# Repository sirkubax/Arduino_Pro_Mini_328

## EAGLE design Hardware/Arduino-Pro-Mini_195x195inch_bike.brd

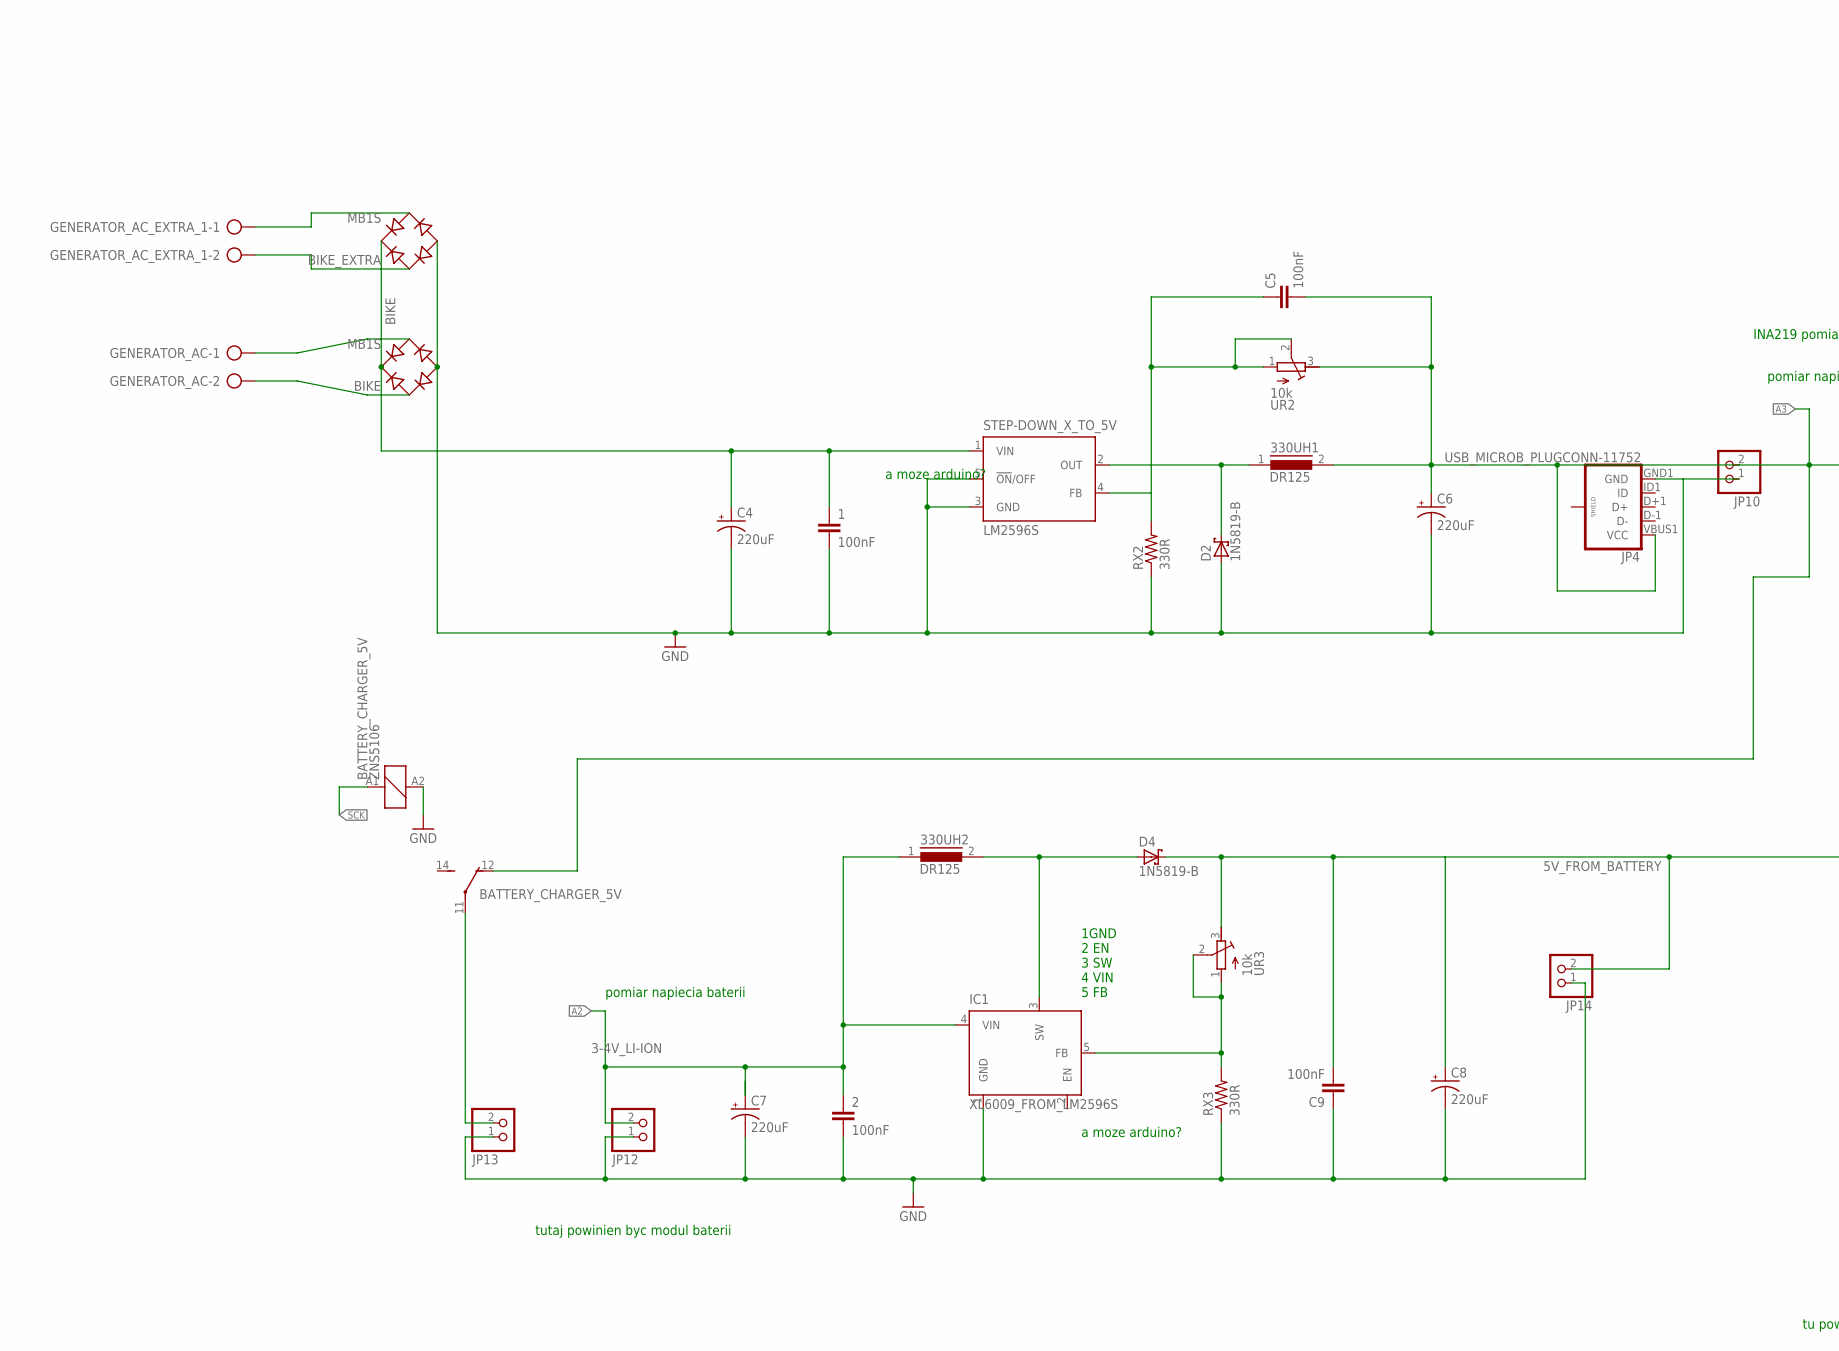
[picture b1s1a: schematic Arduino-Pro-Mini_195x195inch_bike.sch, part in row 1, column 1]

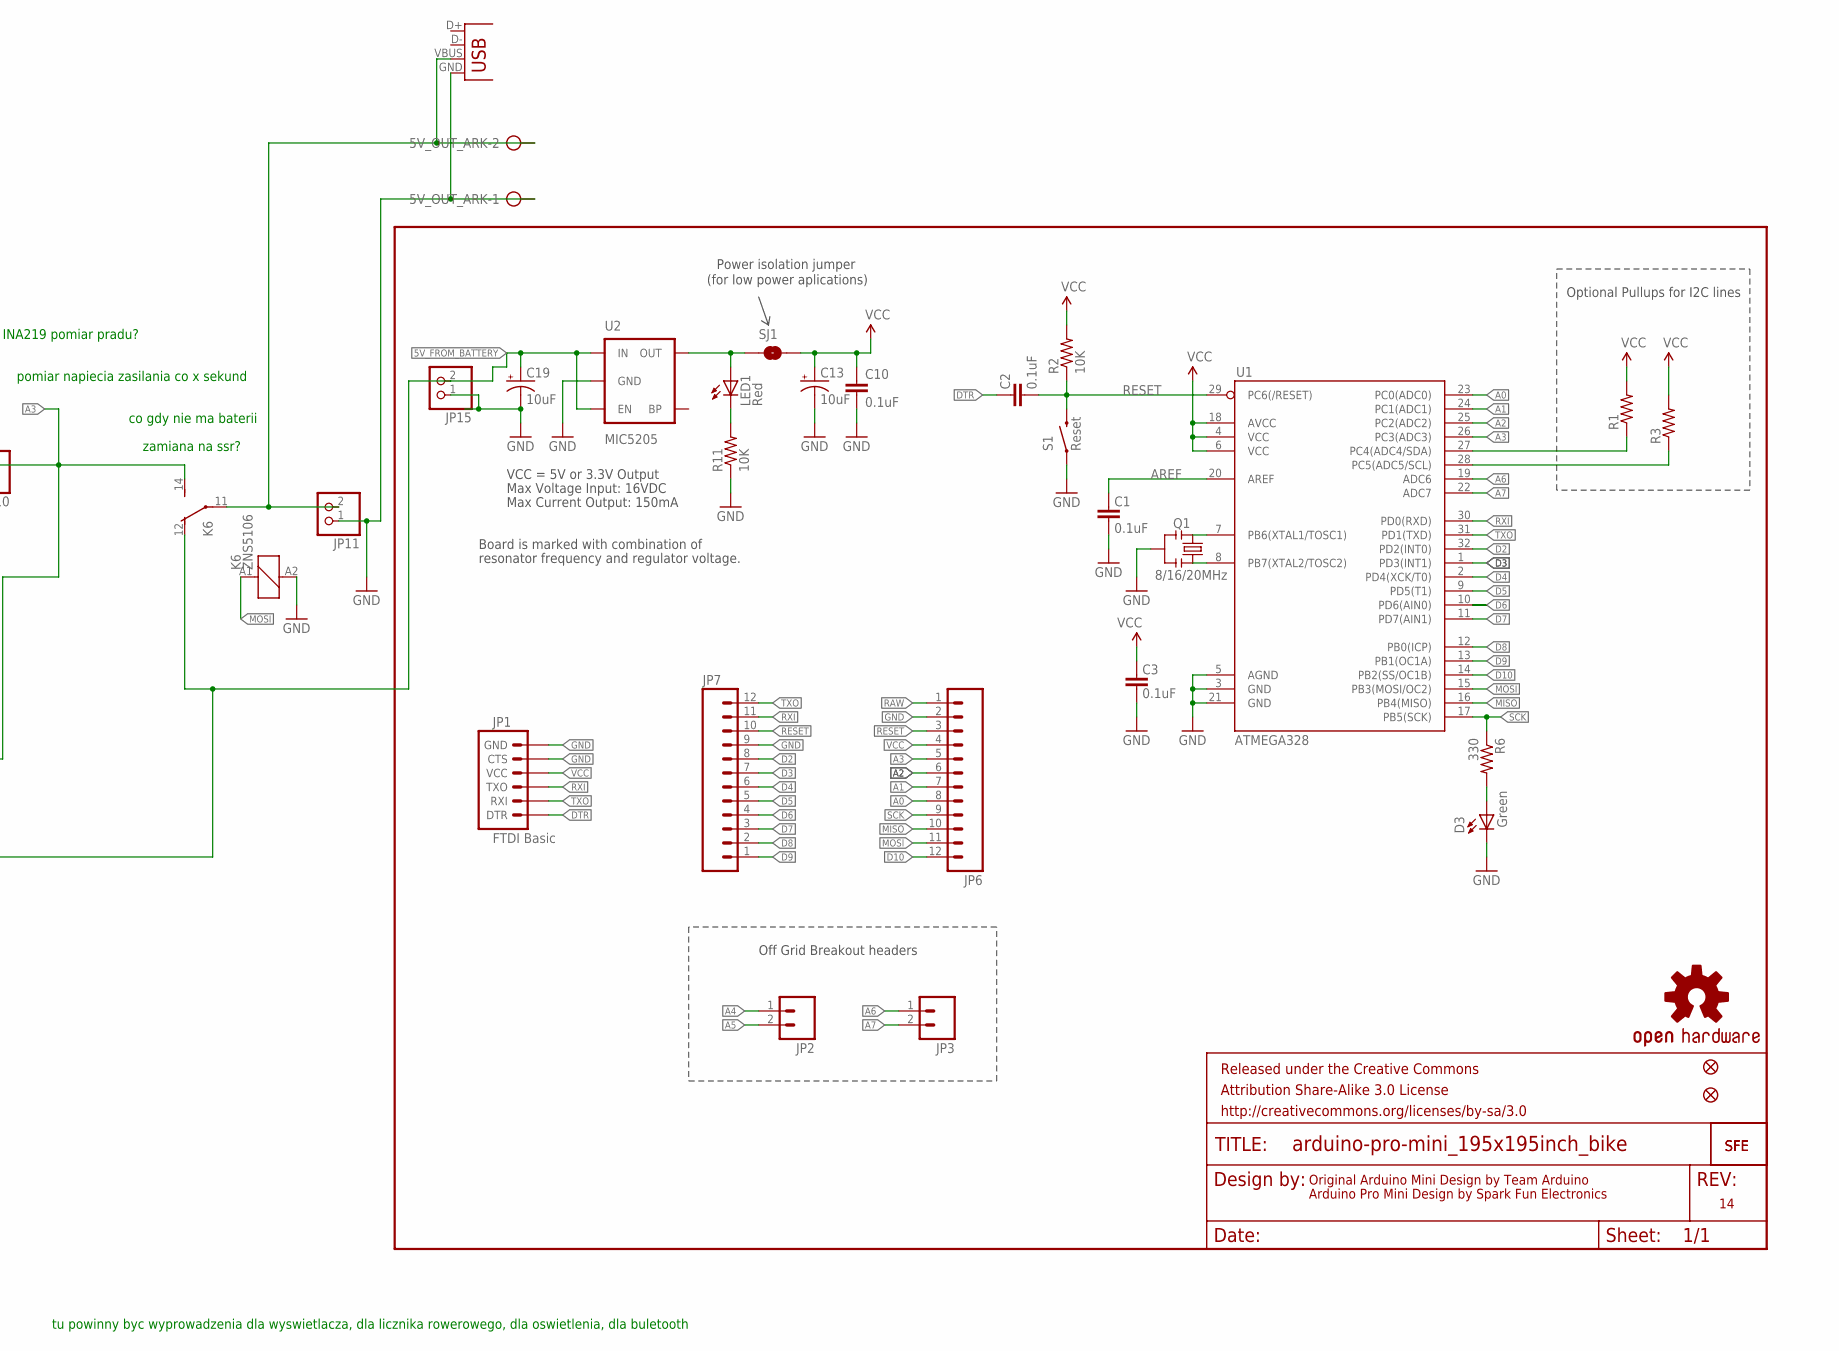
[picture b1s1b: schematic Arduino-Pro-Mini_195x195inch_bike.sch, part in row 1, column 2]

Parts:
1, 2: 100nF; 1206
5V_OUT_ARK: AK300/2
330UH1, 330UH2: DR125
BATTERY_CHARGER_5V: ZNS5106; ZN5
BIKE: MB1S; SOIC-4
BIKE_EXTRA: MB1S; SOIC-4
C1, C2, C3, C10: 0.1uF; 0603-CAP
C4, C6, C7, C8: 220uF; NIC_10X10.5_CAP
C5, C9: 100nF; 1206
C13, C19: 10uF; EIA3216
D2, D4: 1N5819-B; DO41-7.6
D3: Green; 0603-LED-ALT1
FRAME1: FRAME-LETTER; CREATIVE_COMMONS
GENERATOR_AC: AK300/2
GENERATOR_AC_EXTRA_1: AK300/2
IC1: XL6009_FROM_LM2596S; TO263-5
JP1: FTDI Basic; 1X06
JP2, JP3: M02PTH; 1X02
JP4: USB_MICROB_PLUGCONN-11752; USB-B-MICRO-SMD_V03
JP5, JP8: FIDUCIALUFIDUCIAL; MICRO-FIDUCIAL
JP6, JP7: M12PTH; 1X12
JP10, JP11, JP12, JP13, JP14, JP15: PINHD-1X2; 1X02
JP17: USB_; USB-A-S-SILK-FEMALE
K6: ZNS5106; ZN5
LED1: Red; 0603-LED-ALT1
Q1: 8/16/20MHz; RESONATOR-SMD-1:1
R1, R3: RESISTOR0603-RES; 0603-RES
R2, R11: 10K; 0603-RES
R6: 330; 0603-RES
RX2, RX3: 330R; 0805
S1: Reset; TACTILE-SWITCH-SMD-ALT01
SJ1: SOLDERJUMPERNC; SJ_2S
STEP-DOWN_X_TO_5V: LM2596S; TO263-5
U1: ATMEGA328; TQFP32-08
U2: MIC5205; SOT23-5
U$1: LOGO-SFESK; SFE-LOGO-FLAME
U$3: OSHW-LOGOS; OSHW-LOGO-S
U$11: LOGO-SFENEW; SFE-NEW-WEBLOGO
UR2, UR3: 10k; RTRIM3296W

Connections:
3-4V_LI-ION: 2.1, 330UH2.1, C7.+, IC1.4 (VIN), JP12.2
5V: 330UH1.2, BATTERY_CHARGER_5V.12 (O), C5.2, C6.+, JP4.VBUS1 (VCC), JP10.2, K6.14 (S), UR2.3 (E)
5V_FROM_BATTERY: C8.+, C9.2, C19.A (+), D4.C, JP14.2, JP15.2, K6.12 (O), U2.1 (IN), U2.3 (EN), UR3.3 (E)
A0: JP6.8, U1.23 (PC0(ADC0))
A1: JP6.7, U1.24 (PC1(ADC1))
A2: JP6.6, U1.25 (PC2(ADC2))
A3: JP6.5, U1.26 (PC3(ADC3))
A4: JP2.1, R1.1, U1.27 (PC4(ADC4/SDA))
A5: JP2.2, R3.1, U1.28 (PC5(ADC5/SCL))
A6: JP3.1, U1.19 (ADC6)
A7: JP3.2, U1.22 (ADC7)
AREF: C1.2, U1.20 (AREF)
BIKE: BIKE.~2 (AC2), GENERATOR_AC.1
BIKE+: 1.1, BIKE.+, BIKE_EXTRA.+, C4.+, STEP-DOWN_X_TO_5V.1 (VIN)
D2: JP7.8, U1.32 (PD2(INT0))
D3: JP7.7, U1.1 (PD3(INT1))
D4: JP7.6, U1.2 (PD4(XCK/T0))
D5: JP7.5, U1.9 (PD5(T1))
D6: JP7.4, U1.10 (PD6(AIN0))
D7: JP7.3, U1.11 (PD7(AIN1))
D8: JP7.2, U1.12 (PB0(ICP))
D9: JP7.1, U1.13 (PB1(OC1A))
D10: JP6.12, U1.14 (PB2(SS/OC1B))
DTR: C2.2, JP1.1 (DTR)
GND: 1.2, 2.2, 5V_OUT_ARK.1, BATTERY_CHARGER_5V.A2 (2), BIKE.-, BIKE_EXTRA.-, C1.1, C3.1, C4.-, C6.-, C7.-, C8.-, C9.1, C10.2, C13.C (-), C19.C (-), D2.A, D3.C, IC1.1 (GND), JP1.5 (CTS), JP1.6 (GND), JP4.GND1 (GND), JP6.2, JP7.9, JP10.1, JP11.1, JP12.1, JP13.1, JP14.1, JP15.1, JP17.GND, K6.A2 (2), Q1.2, R11.1, RX2.1, RX3.1, S1.1, S1.2 (1), STEP-DOWN_X_TO_5V.3 (GND), STEP-DOWN_X_TO_5V.5 (!ON!/OFF), U1.3 (GND), U1.5 (AGND), U1.21 (GND), U2.2 (GND)
MISO: JP6.10, U1.16 (PB4(MISO))
MOSI: JP6.11, U1.15 (PB3(MOSI/OC2))
unnamed: Q1.3, U1.8 (PB7(XTAL2/TOSC2))
unnamed: Q1.1, U1.7 (PB6(XTAL1/TOSC1))
unnamed: LED1.A, SJ1.1, U2.5 (OUT)
unnamed: LED1.C, R11.2
unnamed: 330UH2.2, D4.A, IC1.3 (SW)
unnamed: BIKE.~1 (AC1), GENERATOR_AC.2
unnamed: D3.A, R6.2
unnamed: BIKE_EXTRA.~2 (AC2), GENERATOR_AC_EXTRA_1.1
unnamed: BIKE_EXTRA.~1 (AC1), GENERATOR_AC_EXTRA_1.2
unnamed: C5.1, RX2.2, STEP-DOWN_X_TO_5V.4 (FB), UR2.1 (A), UR2.2 (S)
unnamed: BATTERY_CHARGER_5V.11, JP13.2
unnamed: 330UH1.1, D2.C, STEP-DOWN_X_TO_5V.2 (OUT)
unnamed: IC1.5 (FB), RX3.2, UR3.1 (A), UR3.2 (S)
unnamed: 5V_OUT_ARK.2, JP11.2, JP17.VBUS, K6.11
RAW: JP6.1
RESET: C2.1, JP6.3, JP7.10, R2.1, S1.3 (2), S1.4 (2), U1.29 (PC6(/RESET))
RXI: JP1.3 (TXO), JP7.11, U1.30 (PD0(RXD))
SCK: JP6.9, R6.1, U1.17 (PB5(SCK))
TXO: JP1.2 (RXI), JP7.12, U1.31 (PD1(TXD))
VCC: C3.2, C10.1, C13.A (+), JP1.4 (VCC), JP6.4, R1.2, R2.2, R3.2, SJ1.2, U1.4 (VCC), U1.6 (VCC), U1.18 (AVCC)

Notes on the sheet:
Original Arduino Mini Design by Team Arduino
Arduino Pro Mini Design by Spark Fun Electronics
Max Voltage Input: 16VDC
Max Current Output: 150mA
Board is marked with combination of
resonator frequency and regulator voltage.
VCC = 5V or 3.3V Output
Optional Pullups for I2C lines
Off Grid Breakout headers
Power isolation jumper
(for low power aplications)
1GND 2 EN 3 SW 4 VIN 5 FB
a moze arduino?
tutaj powinien byc modul baterii
tu powinny byc wyprowadzenia dla wyswietlacza, dla licznika rowerowego, dla oswietlenia, dla buletooth
pomiar napiecia zasilania co x sekund
pomiar napiecia baterii
INA219 pomiar pradu?
zamiana na ssr?
co gdy nie ma baterii

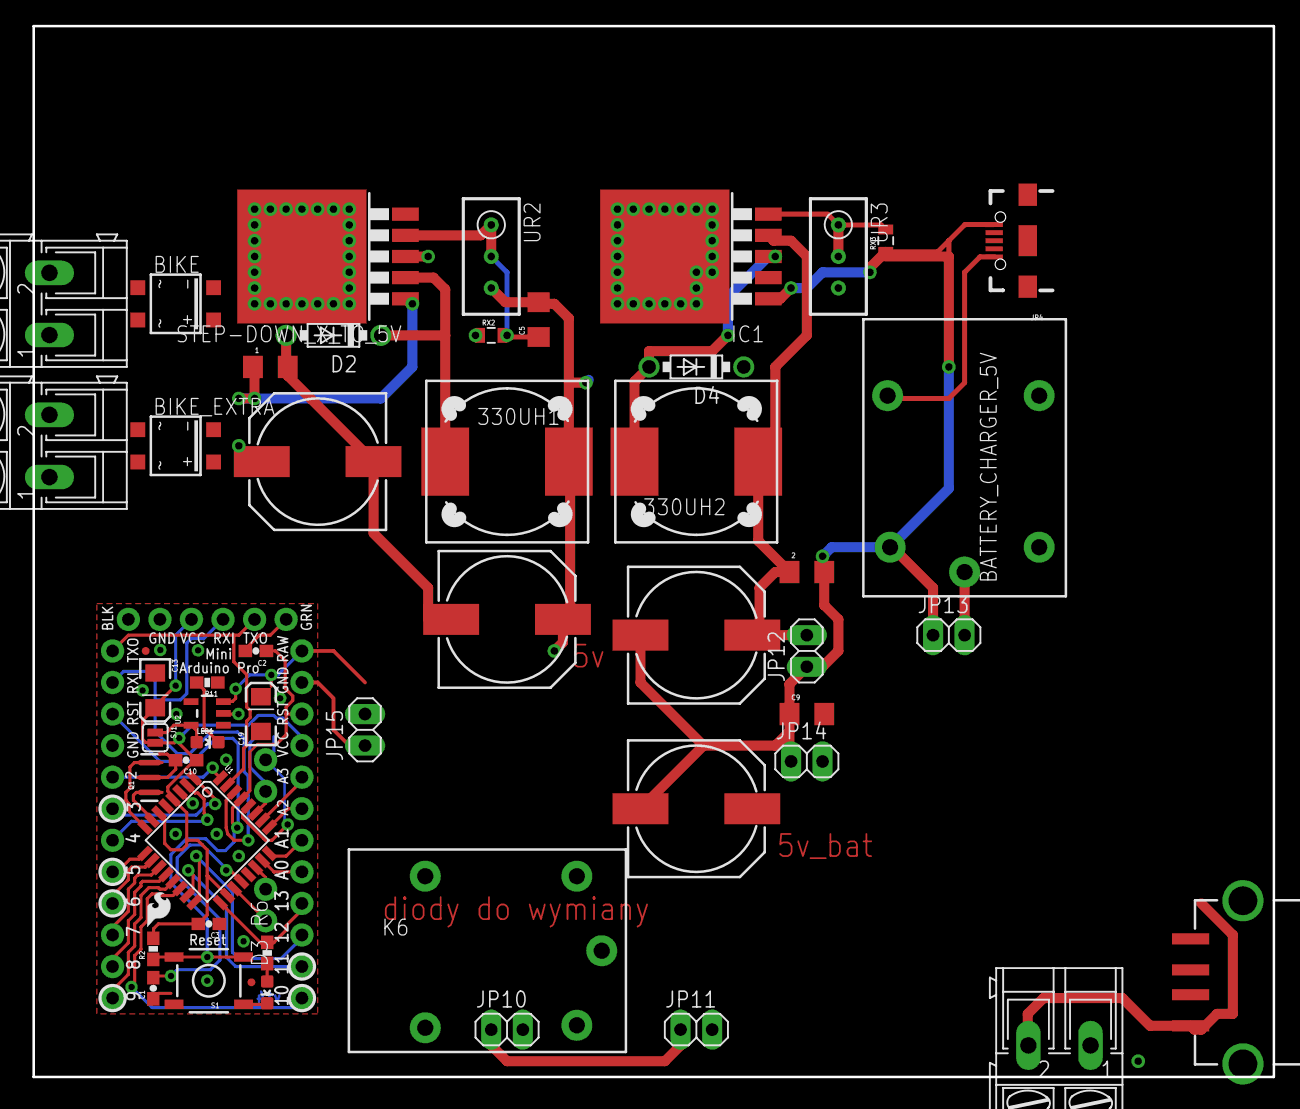
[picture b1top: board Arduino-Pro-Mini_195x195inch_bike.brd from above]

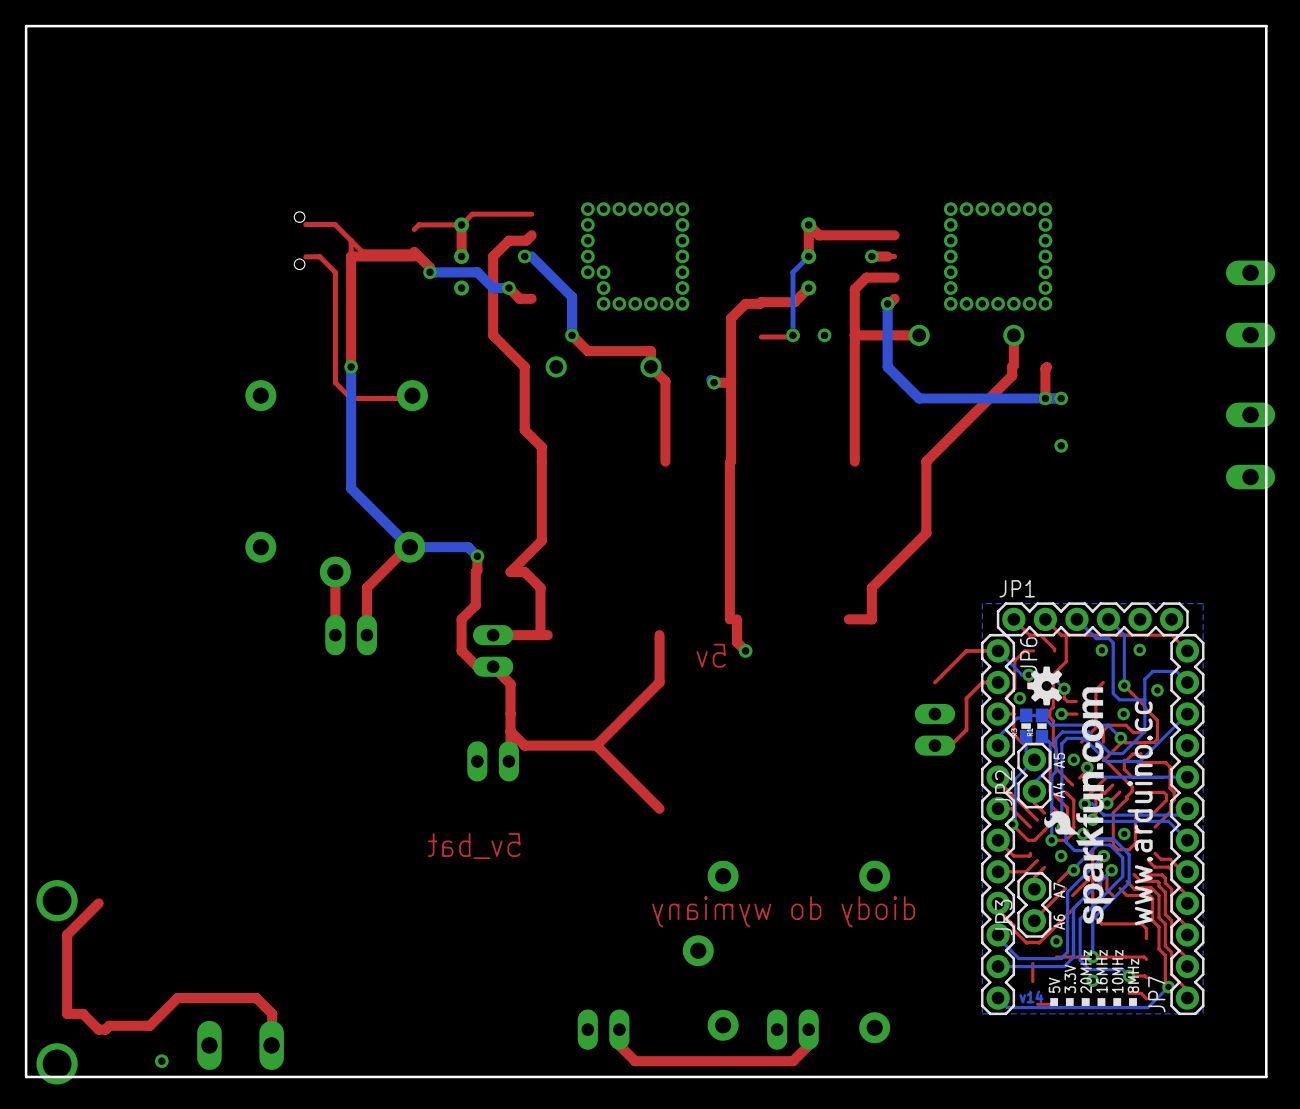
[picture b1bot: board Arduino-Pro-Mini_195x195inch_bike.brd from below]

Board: 2 copper layers, 99.8 x 84.6 mm, 62 parts (9 on the bottom side), 46 nets.

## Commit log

2015-02-17 1.95x1.95 board dimensions
2015-02-19 drafts
2015-02-28 bikeups
2015-03-27 some work, not ready
2015-03-29 before ground
2015-03-29 work update, bike draft

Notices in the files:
parts and their libraries:
SparkFun-Aesthetics: Licensing: CC v3.0 Share-Alike You are welcome to use this library for commercial purposes.
SparkFun-Aesthetics: Released under the Creative Commons Attribution Share-Alike 3.0 License
SparkFun-Aesthetics: http://creativecommons.org/licenses/by-sa/3.0
